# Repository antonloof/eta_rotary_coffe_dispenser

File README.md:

# eta_rotary_coffe_dispenser
Dagny 2.0. Även kännd som ETAs kaffedispenser med gammal teknik

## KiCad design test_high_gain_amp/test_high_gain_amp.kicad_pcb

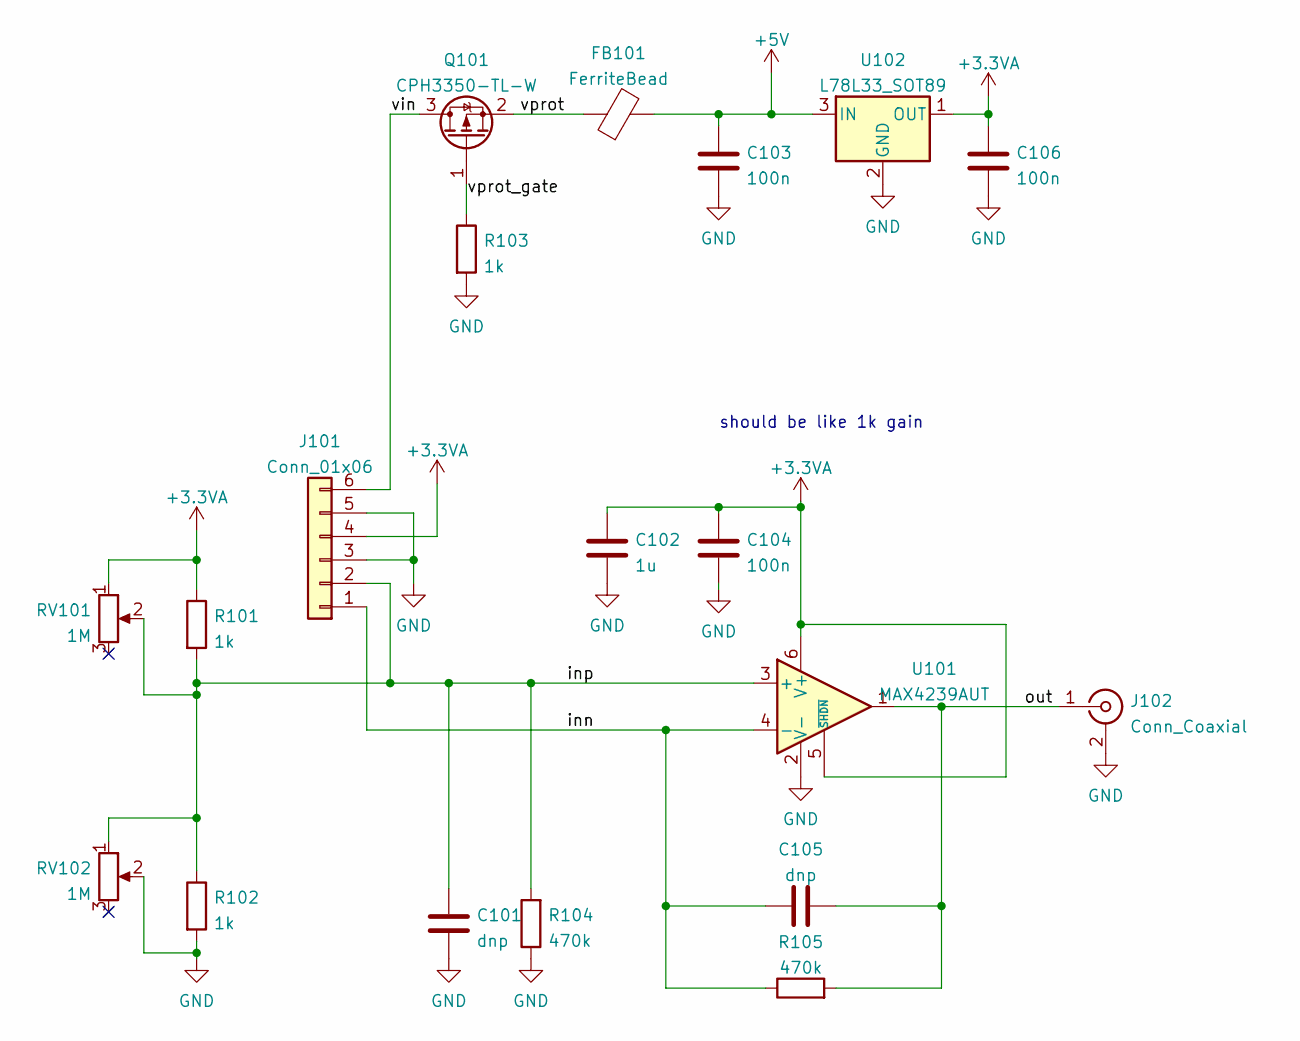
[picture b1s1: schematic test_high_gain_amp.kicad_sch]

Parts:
C101, C105: dnp; C_0603_1608Metric_Pad1.08x0.95mm_HandSolder
C102: 1u; C_0603_1608Metric_Pad1.08x0.95mm_HandSolder
C103, C104, C106: 100n; C_0603_1608Metric_Pad1.08x0.95mm_HandSolder
FB101: FerriteBead; L_0603_1608Metric_Pad1.05x0.95mm_HandSolder
J101: Conn_01x06; TerminalBlock_bornier-6_P5.08mm
J102: Conn_Coaxial; BNC_Amphenol_B6252HB-NPP3G-50_Horizontal
Q101: CPH3350-TL-W; SOT-23_Handsoldering
R101, R102, R103: 1k; R_0603_1608Metric_Pad0.98x0.95mm_HandSolder
R104, R105: 470k; R_0603_1608Metric_Pad0.98x0.95mm_HandSolder
RV101, RV102: 1M; Potentiometer_ACP_CA6-H2,5_Horizontal
U101: MAX4239AUT; SOT-23-6
U102: L78L33_SOT89; SOT-89-3

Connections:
+3.3VA: C102.1, C104.1, C106.1, J101.4, R101.1, RV101.1, U101.5 (~SHDN), U101.6 (V+), U102.1 (OUT)
+5V: C103.1, FB101.2, U102.3 (IN)
/inn: C105.1, J101.1, R105.1, U101.4 (-)
/inp: C101.2, J101.2, R101.2, R102.1, R104.2, RV101.2, RV102.1, U101.3 (+)
/out: C105.2, J102.1 (In), R105.2, U101.1
/vin: J101.6, Q101.3 (D)
/vprot: FB101.1, Q101.2 (S)
/vprot_gate: Q101.1 (G), R103.1
GND: C101.1, C102.2, C103.2, C104.2, C106.2, J101.3, J101.5, J102.2 (Ext), R102.2, R103.2, R104.1, RV102.2, U101.2 (V-), U102.2 (GND)

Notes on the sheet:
should be like 1k gain

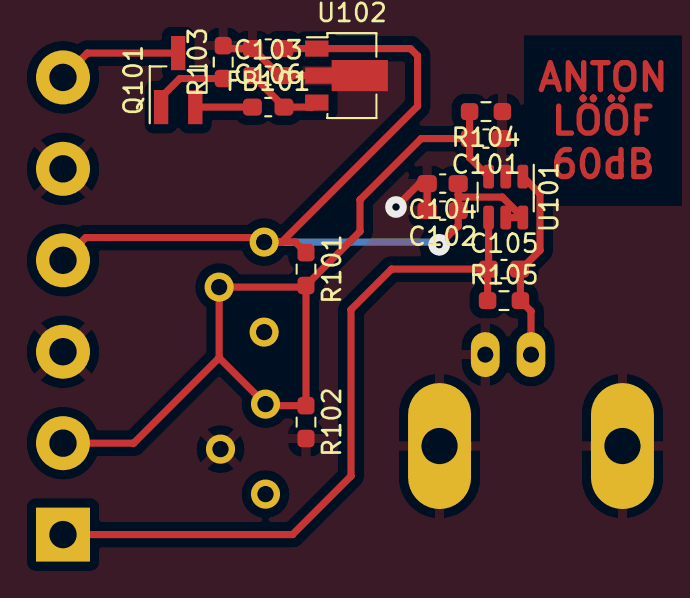
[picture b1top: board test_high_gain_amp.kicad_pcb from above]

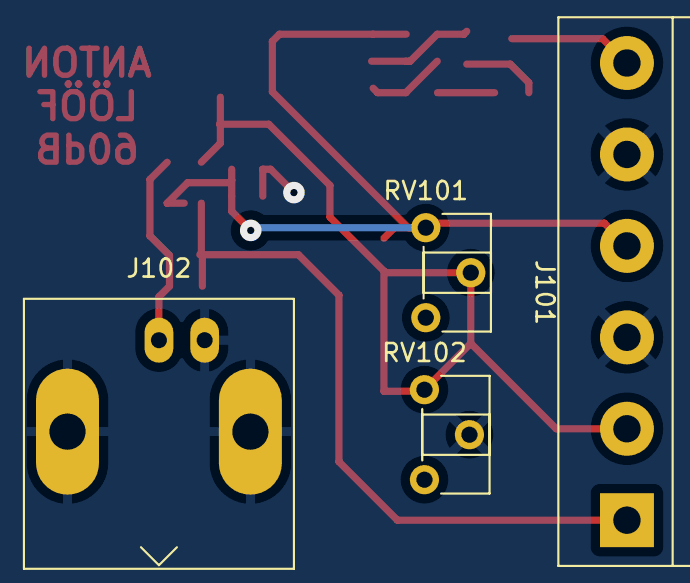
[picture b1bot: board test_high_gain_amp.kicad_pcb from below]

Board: 2 copper layers, 19 parts (4 on the bottom side), 9 nets.

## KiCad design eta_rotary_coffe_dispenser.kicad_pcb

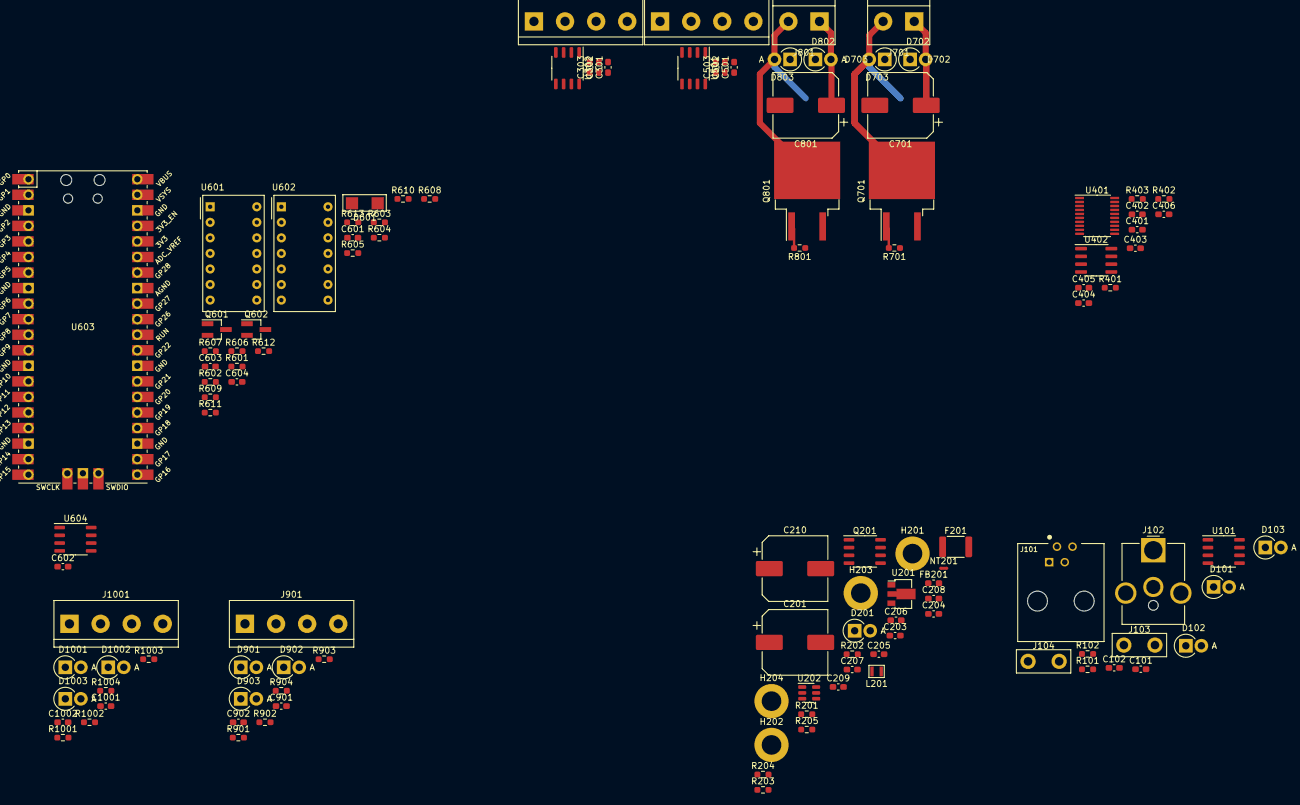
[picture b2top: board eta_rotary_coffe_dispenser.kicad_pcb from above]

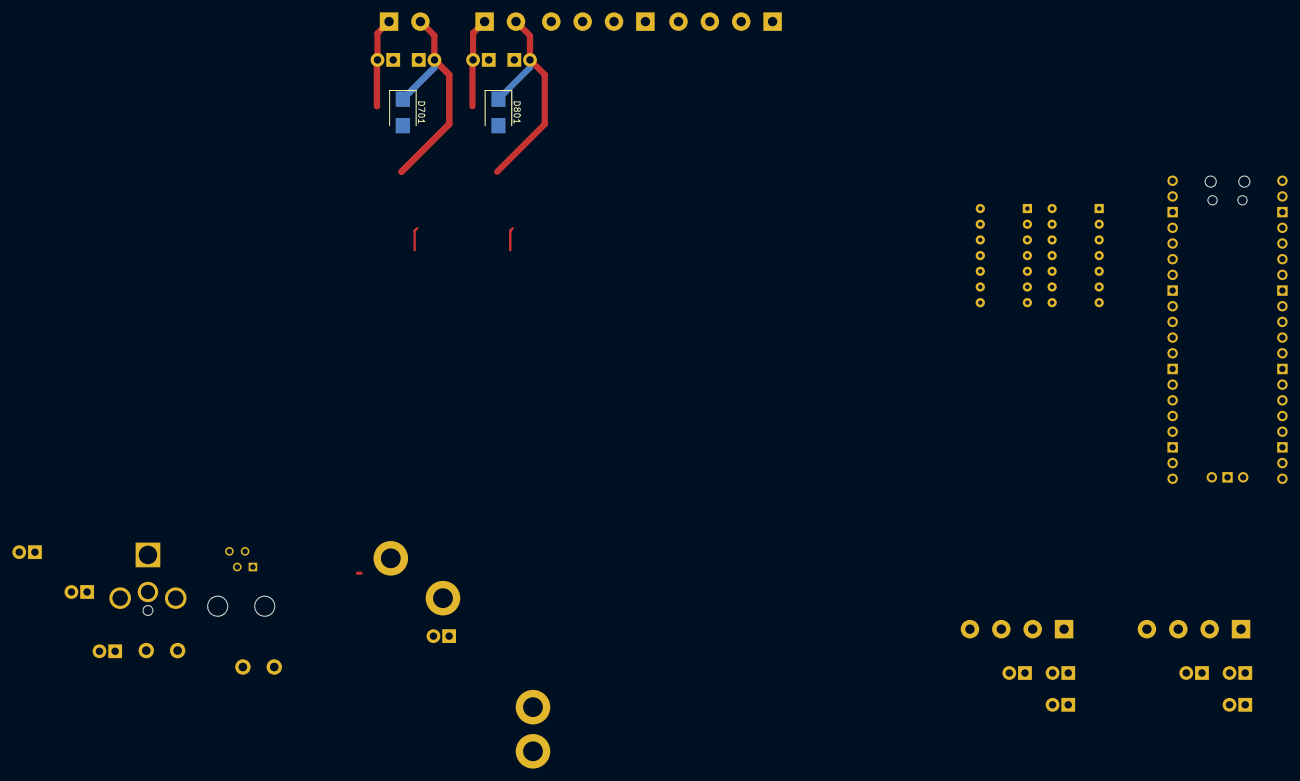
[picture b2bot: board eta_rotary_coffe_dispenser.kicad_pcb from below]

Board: 2 copper layers, 117 parts (2 on the bottom side), 75 nets.

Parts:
C101, C301, C401, C405, C501, C601: 1u; C_0603_1608Metric_Pad1.08x0.95mm_HandSolder
C102, C204, C205, C206, C302, C402, C403, C404, C406, C502, C602, C901, C902, C1001, C1002: 100n; C_0603_1608Metric_Pad1.08x0.95mm_HandSolder
C201, C210, C701, C801: 470u; CP_Elec_10x10.5
C203: 1u 25V; C_0603_1608Metric_Pad1.08x0.95mm_HandSolder
C207: dni; C_0603_1608Metric_Pad1.08x0.95mm_HandSolder
C208, C209: 22u; C_0603_1608Metric_Pad1.08x0.95mm_HandSolder
C303, C503, C603, C604: 10n; C_0603_1608Metric_Pad1.08x0.95mm_HandSolder
D101, D102, D103, D702, D703, D802, D803, D901, D902, D903, D1001, D1002, D1003: P6KE16CA+; D_DO-15_P2.54mm_Vertical_AnodeUp
D201: 5v; D_DO-15_P2.54mm_Vertical_AnodeUp
D601: RSX301L-30TE25; SOD-106
D701, D801: SM6T30A; D_SMB
F201: MC36232; Fuse_1812_4532Metric
FB201: FerriteBead; L_0603_1608Metric_Pad1.05x0.95mm_HandSolder
H201, H202, H203, H204: MountingHole_Pad; MountingHole_3.2mm_M3_DIN965_Pad
J101: RJ10; TE_5520257-2
J102: Barrel_Jack; BarrelJack_CUI_PJ-063AH_Horizontal_CircularHoles
J103, J104: SW; TE_726386-2
J301, J501, J901, J1001: Conn_01x04; TerminalBlock_bornier-4_P5.08mm
J701, J801: Conn_01x02; TerminalBlock_bornier-2_P5.08mm
L201: 2u2; smd_inductor_0806_2016metric
NT201: NetTie_2; NetTie-2_SMD_Pad0.5mm
Q201: FDS4435; SO-8_3.9x4.9mm_P1.27mm
Q601, Q602: KST5551; SOT-23_Handsoldering
Q701, Q801: IRF640NPbF; TO-263-2
R101, R102, R201, R202, R205, R401, R402, R403, R613, R901, R902, R1001, R1002: 10k; R_0603_1608Metric_Pad0.98x0.95mm_HandSolder
R203: 2k2; R_0603_1608Metric_Pad0.98x0.95mm_HandSolder
R204: 52k3; R_0603_1608Metric_Pad0.98x0.95mm_HandSolder
R601, R602, R603, R604, R605, R606, R607, R608, R609, R610, R611, R701, R801: 470; R_0603_1608Metric_Pad0.98x0.95mm_HandSolder
R612, R903, R904, R1003, R1004: 1k; R_0603_1608Metric_Pad0.98x0.95mm_HandSolder
U101, U604: LM358; SO-8_3.9x4.9mm_P1.27mm
U201: L78L33_SOT89; SOT-89-3
U202: AP62250; TSOT-23-6
U302, U501: MAX4196; SO-8_3.9x4.9mm_P1.27mm
U401: MCP2515-xST; TSSOP-20_4.4x6.5mm_P0.65mm
U402: MCP2562-E-SN; SOIC-8_3.9x4.9mm_P1.27mm
U601, U602: MAN74A; MAN71A
U603: Pico; RPi_Pico_SMD_TH

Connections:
+3.3VA: C101.1, C102.1, C205.1, C301.1, C302.1, C303.1, C501.1, C502.1, C503.1, C601.1, C602.1, J301.4, J501.4, R101.1, R612.1, U101.8 (V+), U201.1 (OUT), U302.7 (VCC), U302.8 (~SHND), U501.7 (VCC), U501.8 (~SHND), U604.8 (V+)
+3V3: C401.1, C402.1, C404.1, D903.2 (A2), D1003.2 (A2), J901.1, J901.2, J1001.1, J1001.2, R402.1, R403.1, U401.20 (VDD), U402.5 (Vio), U603.36 (3V3)
+5V: C208.1, C209.1, C405.1, C406.1, D601.2 (A), FB201.1, L201.2, R204.1, U402.3 (VDD)
+12V: C201.1, C203.1, C210.1, C701.1, C801.1, D201.1 (K), D702.2 (A2), D802.2 (A2), J701.1, J801.1, Q201.1 (S), Q201.2 (S), Q201.3 (S), R202.1, U202.3 (vin)
/ADC0: R611.2, U302.5 (FB), U302.6 (OUT)
/ADC1: R610.2, U501.5 (FB), U501.6 (OUT)
/CANH: D102.2 (A2), J101.2, U402.7 (CANH)
/CANL: D103.2 (A2), J101.3, U402.6 (CANL)
/CAN_CLK: U401.9 (OSC1), U603.27 (GPIO21)
/MOTOR_CTRL: R801.1, U603.26 (GPIO20)
/ROTARY_COFFEE0: C1001.1, R1001.1, R1003.1, U603.22 (GPIO17)
/ROTARY_COFFEE1: C1002.1, R1002.1, R1004.1, U603.21 (GPIO16)
/ROTARY_WATER0: C901.1, R901.1, R903.1, U603.25 (GPIO19)
/ROTARY_WATER1: C902.1, R902.1, R904.1, U603.24 (GPIO18)
/SOLENOID_CTRL: R701.1, U603.29 (GPIO22)
/SPI_CIPO: U401.17 (SO), U603.1 (GPIO0)
/SPI_COPI: U401.16 (SI), U603.5 (GPIO3)
/SPI_SCK: U401.14 (SCK), U603.4 (GPIO2)
/VIN: D101.2 (A2), J102.1, J103.1
/VIN_SW: F201.1, J104.1
/VREF0: U101.1, U101.2 (-), U302.1 (REF)
/VREF1: U101.6 (-), U101.7, U501.1 (REF)
/can/can_osc_out: R401.1, U401.8 (OSC2)
/can/can_rst: C403.1, R403.2, U401.19 (~RESET)
/can/rxcan: U401.2 (RXCAN), U402.4 (RXD)
/can/txcan: U401.1 (TXCAN), U402.1 (TXD)
/coffee_rotary/ROTARY0_IN: D1001.2 (A2), J1001.3, R1003.2
/coffee_rotary/ROTARY1_IN: D1002.2 (A2), J1001.4, R1004.2
/cpu/7SEG_A: R603.1, U601.14 (A), U602.14 (A)
/cpu/7SEG_A_PRER: R603.2, U603.12 (GPIO9)
/cpu/7SEG_B: R604.1, U601.13 (B), U602.13 (B)
/cpu/7SEG_B_PRER: R604.2, U603.14 (GPIO10)
/cpu/7SEG_C: R605.1, U601.8 (C), U602.8 (C)
/cpu/7SEG_C_PRER: R605.2, U603.15 (GPIO11)
/cpu/7SEG_D: R606.1, U601.7 (D), U602.7 (D)
/cpu/7SEG_DIG0: Q602.3 (C), U602.4 (CC), U602.12 (CC)
/cpu/7SEG_DIG0_BASE: Q602.1 (B), R601.1
/cpu/7SEG_DIG0_PRER: R601.2, U603.10 (GPIO7)
/cpu/7SEG_DIG1: Q601.3 (C), U601.4 (CC), U601.12 (CC)
/cpu/7SEG_DIG1_BASE: Q601.1 (B), R602.1
/cpu/7SEG_DIG1_PRER: R602.2, U603.11 (GPIO8)
/cpu/7SEG_D_PRER: R606.2, U603.16 (GPIO12)
/cpu/7SEG_E: R607.1, U601.6 (E), U602.6 (E)
/cpu/7SEG_E_PRER: R607.2, U603.17 (GPIO13)
/cpu/7SEG_F: R608.1, U601.1 (F), U602.1 (F)
/cpu/7SEG_F_PRER: R608.2, U603.19 (GPIO14)
/cpu/7SEG_G: R609.1, U601.2 (G), U602.2 (G)
/cpu/7SEG_G_PRER: R609.2, U603.20 (GPIO15)
/cpu/ADC_VREF: U603.35 (ADC_VREF), U604.1, U604.2 (-), U604.6 (-), U604.7
/cpu/ADC_VREF_DIV: R612.2, R613.1, U604.3 (+), U604.5 (+)
/cpu/PICO_ADC0: C604.1, R611.1, U603.31 (GPIO26_ADC0)
/cpu/PICO_ADC1: C603.1, R610.1, U603.32 (GPIO27_ADC1)
/cpu/VSYS: D601.1 (K), U603.39 (VSYS)
/motor/EXT_CTRL: Q801.1 (G), R801.2
/motor/EXT_OUT: D801.1 (K), D803.2 (A2), J801.2, Q801.2 (D)
/power/3v3a_regin: C204.1, FB201.2, U201.3 (IN)
/power/VFUSE: F201.2, Q201.5 (D), Q201.6 (D), Q201.7 (D), Q201.8 (D)
/power/reg_bst: C206.1, U202.6 (bst)
/power/reg_en: R202.2, R203.1, U202.5 (en)
/power/reg_fb: C207.1, R204.2, R205.1, U202.4 (fb)
/power/reg_sw: C206.2, L201.1, U202.2 (sw)
/power/vprot_gate: D201.2 (A), Q201.4 (G), R201.1
/scale_amp1/INN: J501.2, U501.2 (IN-)
/scale_amp1/INP: J501.1, U501.3 (IN+)
/scale_amp/INN: J301.2, U302.2 (IN-)
/scale_amp/INP: J301.1, U302.3 (IN+)
/solenoid/EXT_CTRL: Q701.1 (G), R701.2
/solenoid/EXT_OUT: D701.1 (K), D703.2 (A2), J701.2, Q701.2 (D)
/vref_div: R101.2, R102.1, U101.3 (+), U101.5 (+)
/water_rotary/ROTARY0_IN: D901.2 (A2), J901.3, R903.2
/water_rotary/ROTARY1_IN: D902.2 (A2), J901.4, R904.2
/~CAN_INT: R402.2, U401.13 (~INT), U603.6 (GPIO4)
/~SPI_CS: U401.18 (~CS), U603.2 (GPIO1)
GND: C201.2, C203.2, C204.2, C205.2, C207.2, C208.2, C209.2, C210.2, C401.2, C402.2, C403.2, C404.2, C405.2, C406.2, C701.2, C801.2, C901.2, C902.2, C1001.2, C1002.2, D101.1 (A1), D102.1 (A1), D103.1 (A1), D701.2 (A), D702.1 (A1), D703.1 (A1), D801.2 (A), D802.1 (A1), D803.1 (A1), D901.1 (A1), D902.1 (A1), D903.1 (A1), D1001.1 (A1), D1002.1 (A1), D1003.1 (A1), H201.1, H202.1, H203.1, H204.1, J102.2, NT201.1, Q601.2 (E), Q602.2 (E), Q701.3 (S), Q801.3 (S), R201.2, R203.2, R205.2, R401.2, R901.2, R902.2, R1001.2, R1002.2, U201.2 (GND), U202.1 (gnd), U401.10 (VSS), U402.2 (VSS), U402.8 (STBY), U603.3 (GND), U603.8 (GND), U603.13 (GND), U603.18 (GND), U603.23 (GND), U603.28 (GND), U603.38 (GND), U603.42 (GND)
GNDA: C101.2, C102.2, C301.2, C302.2, C303.2, C501.2, C502.2, C503.2, C601.2, C602.2, C603.2, C604.2, J301.3, J501.3, NT201.2, R102.2, R613.2, U101.4 (V-), U302.4 (VEE), U501.4 (VEE), U603.33 (AGND), U604.4 (V-)

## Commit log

2022-03-26 Is done
2022-06-20 start rev 2 op project with can and weight sens
2022-06-20 add missing files
2022-06-20 some form of schematic done, still lots to test
2022-06-21 add test board for x1000 amp
2022-06-21 Finish 60dB amp prototype
2022-06-22 test amp
